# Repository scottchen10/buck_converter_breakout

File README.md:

# MIC24066 Buck Converter Breakout

A simple breakout board for the Microchip MIC24066 synchronous buck converter designed in KiCad.

This was a learning project so there may be many improvements that are possible.

## 3D View

## Schematic

- [`MIC24066_Schematic.pdf`](docs/MIC24066_Schematic.pdf)

## PCB Layout

### Top Layer

### Bottom Layer

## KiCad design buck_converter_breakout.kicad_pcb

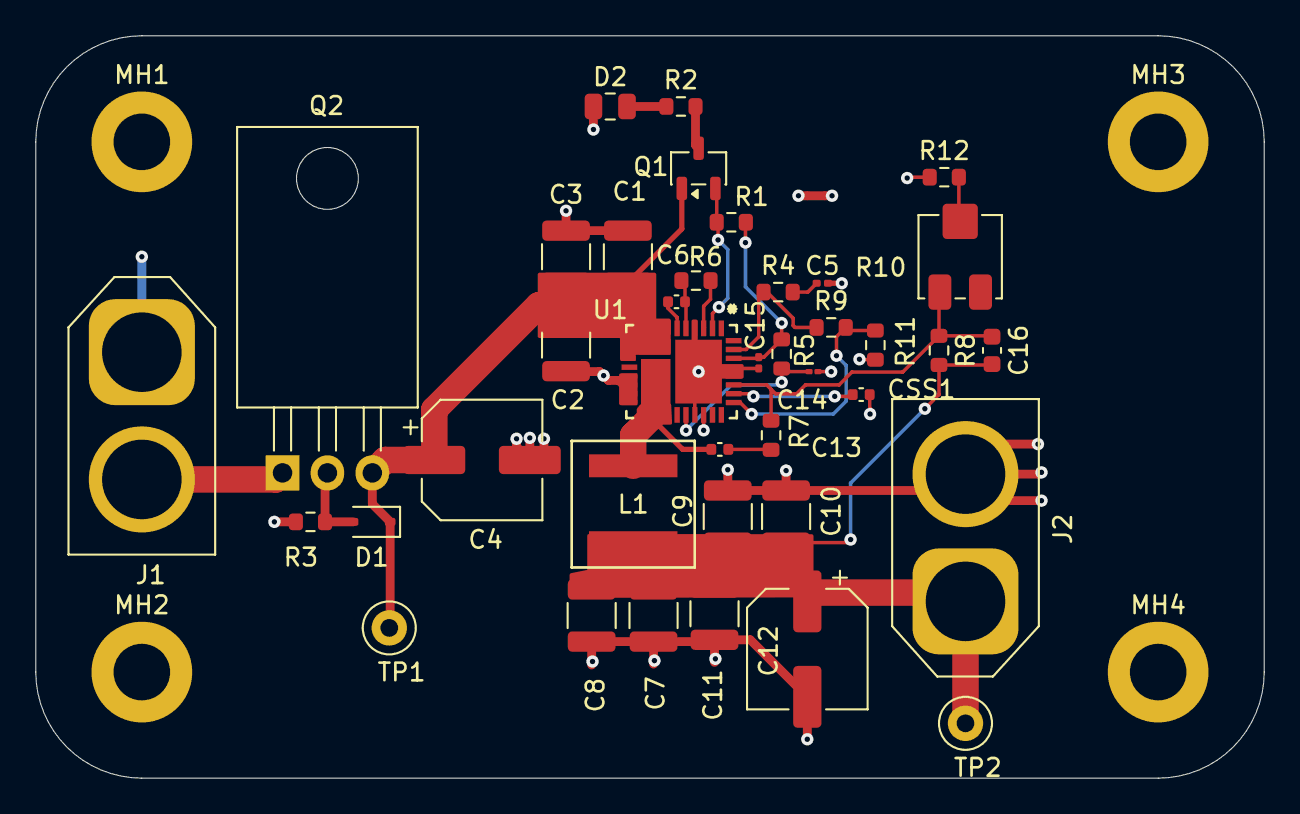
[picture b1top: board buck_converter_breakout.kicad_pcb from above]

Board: 4 copper layers, 69.5 x 42.0 mm, 44 parts (0 on the bottom side), 20 nets.

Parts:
C1, C2, C3: 4u7; C_1210_3225Metric
C4, C12: 47u; CP_Elec_6.3x7.7
C5: 0u1; C_0201_0603Metric
C6: 0u1; C_0402_1005Metric
C7, C8, C9, C10, C11: 47u; C_1210_3225Metric
C13: 47n; C_0402_1005Metric
C14: 4u7; C_01005_0402Metric
C15: 2u2; C_0201_0603Metric
C16: 1n0; C_0603_1608Metric
CSS1: 2n2; C_0402_1005Metric
D1: D_Zener; D_SOD-323
D2: LED; C_0805_2012Metric
J1: Input Connector; AMASS_XT60-F_1x02_P7.20mm_Vertical
J2: Output Connector; AMASS_XT60-F_1x02_P7.20mm_Vertical
L1: 3.3uH; XGL6060-332MEC
MH1, MH2, MH3, MH4: M3; MountingHole_3.2mm_M3_ISO7380_Pad
NT1: NetTie_2; NetTie-2_SMD_Pad0.5mm
Q1: NMOS; SOT-23-3
Q2: FQP47P06; TO-220-3_Horizontal_TabDown
R1, R5: 10k; R_0603_1608Metric
R2: 5k; R_0603_1608Metric
R3, R9, R11: 100k; R_0603_1608Metric
R4: 0; R_0603_1608Metric
R6: 1k; R_0603_1608Metric
R7: 43k; R_0603_1608Metric
R8: 15k; R_0603_1608Metric
R10: 5k; Potentiometer_Bourns_3314J_Vertical
R12: 505; R_0603_1608Metric
TP1: M3 VIN; TestPoint_Loop_D2.50mm_Drill1.0mm
TP2: M3 VOUT; TestPoint_Loop_D2.50mm_Drill1.0mm
U1: MIC24066T-E/QNA; VQFN36_QNA_MCH

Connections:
/SW: C6.2, C13.1, L1.1, R6.1, U1.5 (SW), U1.19 (SW), U1.20 (SW), U1.21 (SW), U1.22 (SW), U1.39 (SW)
/VOUT: C7.1, C8.1, C9.1, C10.1, C11.1, C12.1, C16.1, J2.1, L1.2, R8.1, TP2.1 (1_1)
AGND: C5.1, C15.2, CSS1.2, NT1.1, R11.2, R12.2, U1.4 (AGND), U1.25 (AGND), U1.32 (AGND), U1.33 (AGND), U1.37 (AGND)
unnamed: C5.2, R4.1
unnamed: C13.2, R7.1
unnamed: D1.2 (A), Q2.2 (G), R3.1
unnamed: D2.2 (A), R2.2
unnamed: J1.2, Q2.1 (D)
unnamed: Q1.2 (G), R1.2, U1.2 (PG)
unnamed: Q1.3 (S), R2.1
unnamed: R10.2, R12.1
unnamed: C6.1, U1.6 (BST)
unnamed: C16.2, R7.2, R8.2, R10.1, U1.31 (FB)
unnamed: R9.2, R11.1, U1.29 (FREQ)
unnamed: R6.2, U1.3 (ILIM)
unnamed: C14.1, R5.1, U1.24 (PVDD)
unnamed: CSS1.1, U1.30 (SS)
PGND: C1.2, C2.2, C3.2, C4.2, C7.2, C8.2, C9.2, C10.2, C11.2, C12.2, C14.2, D2.1 (K), J1.1, J2.2, MH1.1 (1_1), MH2.1 (1_1), MH3.1 (1_1), MH4.1 (1_1), NT1.2, R3.2, U1.15 (PGND), U1.16 (PGND), U1.17 (PGND), U1.18 (PGND), U1.26 (EXTVDD)
VDD: C15.1, R1.1, R5.2, U1.34 (VDD)
VIN: C1.1, C2.1, C3.1, C4.1, D1.1 (K), Q1.1 (D), Q2.3 (S), R4.2, R9.1, TP1.1 (1_1), U1.7 (VIN), U1.8 (VIN), U1.9 (VIN), U1.10 (VIN), U1.11 (VIN), U1.12 (VIN), U1.13 (VIN), U1.27 (EN), U1.35 (SVIN), U1.38 (VIN)

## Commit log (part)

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2026-06-15 added mic24066 reference design
2026-06-22 added pg led, reverse polarity protection
